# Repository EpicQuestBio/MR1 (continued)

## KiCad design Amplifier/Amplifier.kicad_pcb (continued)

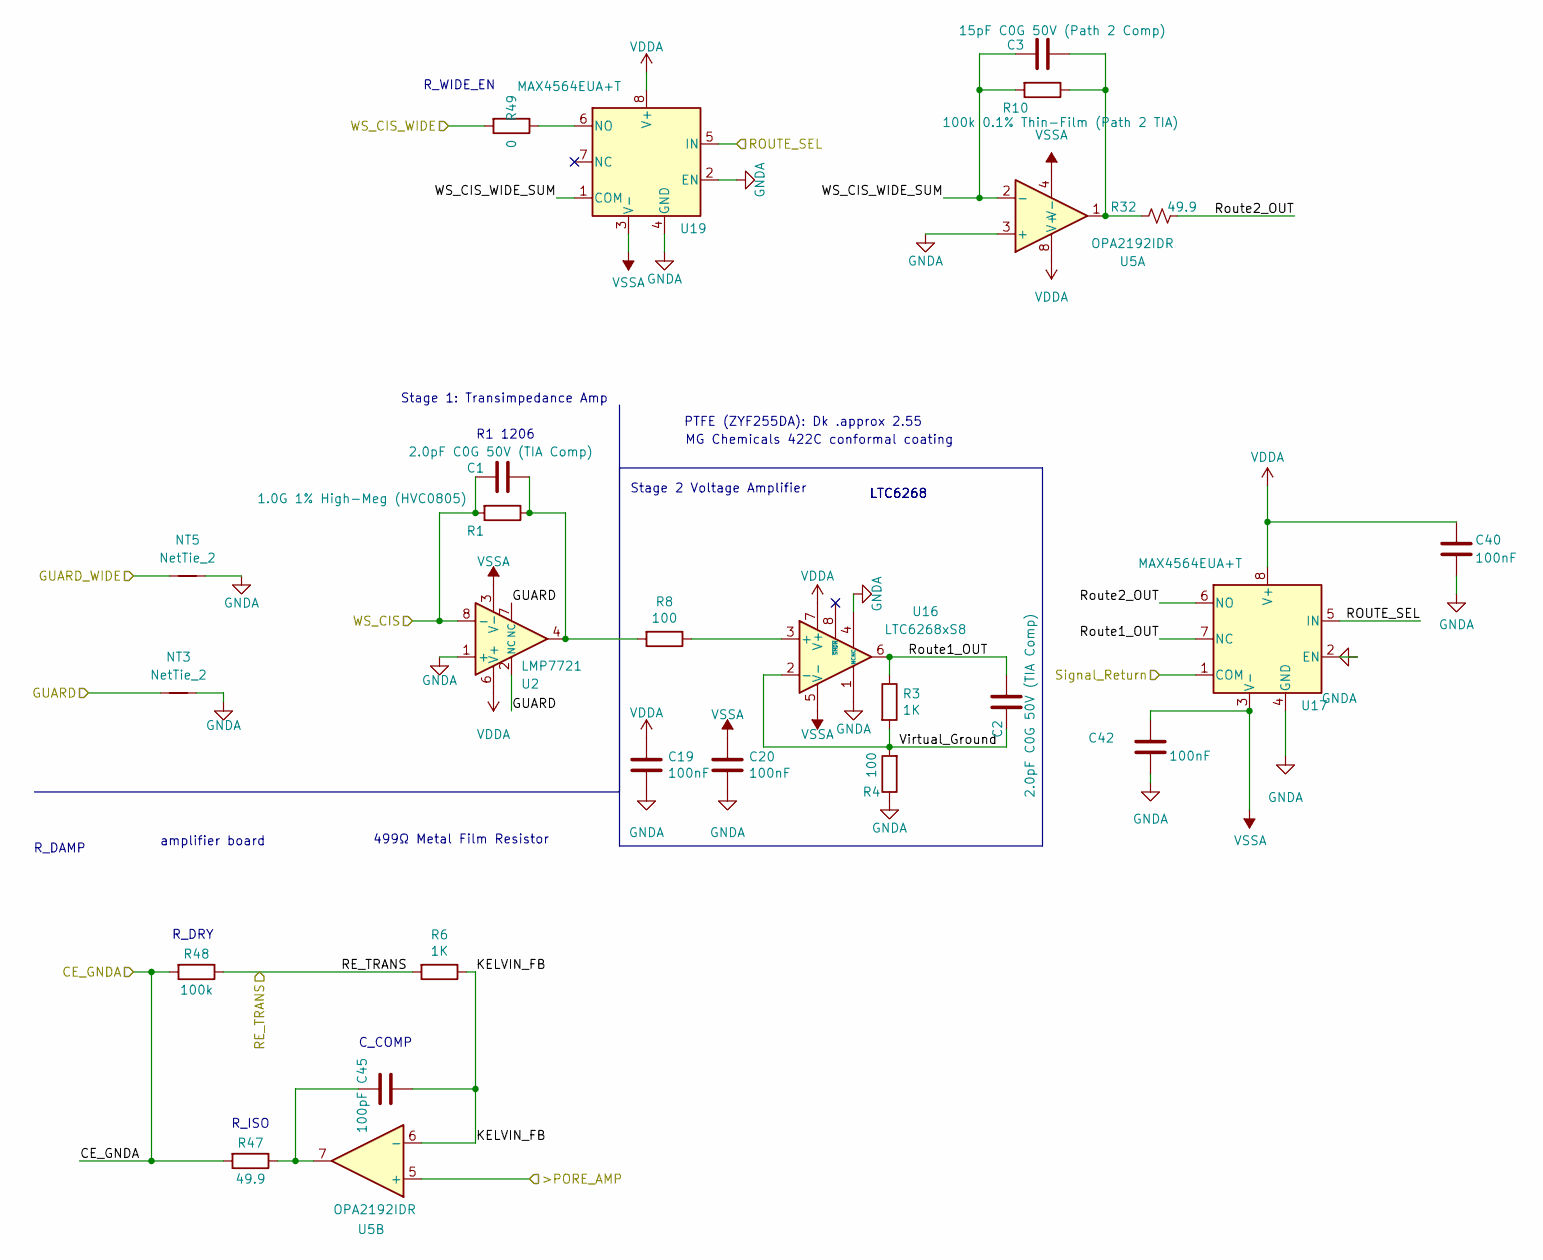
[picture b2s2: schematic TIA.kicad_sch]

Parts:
C1, C2: 2.0pF C0G 50V (TIA Comp); C_0402_1005Metric; LCSC C161316
C3: 15pF C0G 50V (Path 2 Comp); C_0402_1005Metric; LCSC C1548
C19, C20: 100nF; C_0402_1005Metric; LCSC C1525
C40, C42: 100nF; C_0402_1005Metric; Mouser PN 710-885012205037; LCSC C1525
C45: 100pF; C_0402_1005Metric; MPN GRM1555C1H101JA01D; LCSC C1546
NT3, NT5: NetTie_2; NetTie-2_SMD_Pad0.5mm
R1: 1.0G 1% High-Meg (HVC0805); R_0805_2012Metric; LCSC HVC0805T1007JET
R3, R6: 1K; R_0402_1005Metric; LCSC C11702
R4, R8: 100; R_0402_1005Metric; LCSC C25076
R10: 100k 0.1% Thin-Film (Path 2 TIA); R_0402_1005Metric; LCSC C60491
R32: 49.9; R_0402_1005Metric; MPN RC0402JR-0727RL; LCSC C87044
R47: 49.9; R_0402_1005Metric; MPN RC0402FR-0749R9L; LCSC C87044
R48: 100k; R_0402_1005Metric; MPN RC0402FR-07100KL; LCSC C60491
R49: 0; R_0402_1005Metric; MPN RC0402JR-070RL; LCSC C17168
U2: LMP7721; SOIC-8_3.9x4.9mm_P1.27mm; Mouser PN 926-LMP7721MA/NOPB
U5: OPA2192IDR; SOIC-8_3.9x4.9mm_P1.27mm; MPN OPA2192IDR; LCSC C110074
U16: LTC6268xS8; SO-8_3.9x4.9mm_P1.27mm; MPN LTC6268IS8#TRPBF; LCSC C689169
U17, U19: MAX4564EUA+T; MSOP-8_3x3mm_P0.65mm; MPN MAX4564EUA+T; Mouser PN 700-MAX4564EUA+

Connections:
/>PORE_AMP: U5.5 (+); also elsewhere on the board
/CE_GNDA: R47.2, R48.2; also elsewhere on the board
/GUARD: NT3.1, U2.2 (NC), U2.7 (NC); also elsewhere on the board
/GUARD_WIDE: NT5.1; also elsewhere on the board
/RE_TRANS: R6.2, R48.1; also elsewhere on the board
/ROUTE_SEL: U17.5 (IN), U19.5 (IN); also elsewhere on the board
/Signal_Return: U17.1 (COM); also elsewhere on the board
/TIA/KELVIN_FB: C45.2, R6.1, U5.6 (-)
/TIA/Route1_OUT: C2.1, R3.1, U16.6, U17.7 (NC)
/TIA/Route2_OUT: R32.2, U17.6 (NO)
/TIA/Virtual_Ground: C2.2, R3.2, R4.2, U16.2 (-)
/TIA/WS_CIS_WIDE_SUM: C3.2, R10.2, U5.2 (-), U19.1 (COM)
/WS_CIS: C1.2, R1.2, U2.8 (-); also elsewhere on the board
/WS_CIS_WIDE: R49.2; also elsewhere on the board
GNDA: C19.2, C20.2, C40.2, C42.2, NT3.2, NT5.2, R4.1, U2.1 (+), U5.3 (+), U16.1 (NC), U16.4 (NC), U17.2 (EN), U17.4 (GND), U19.2 (EN), U19.4 (GND); also elsewhere on the board
unnamed: C1.1, R1.1, R8.2, U2.4
unnamed: C3.1, R10.1, R32.1, U5.1
unnamed: C45.1, R47.1, U5.7
unnamed: R8.1, U16.3 (+)
unnamed: R49.1, U19.6 (NO)
VDDA: C19.1, C40.1, U2.6 (V+), U5.8 (V+), U16.7 (V+), U17.8 (V+), U19.8 (V+); also elsewhere on the board
VSSA: C20.1, C42.1, U2.3 (V-), U5.4 (V-), U16.5 (V-), U17.3 (V-), U19.3 (V-); also elsewhere on the board

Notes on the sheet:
amplifier board
R_DAMP
LTC6268
499Ω Metal Film Resistor
C_COMP
R1 1206
PTFE (ZYF255DA): Dk .approx 2.55
R_WIDE_EN
Stage 1: Transimpedance Amp
R_DRY
MG Chemicals 422C conformal coating
R_ISO
Stage 2 Voltage Amplifier

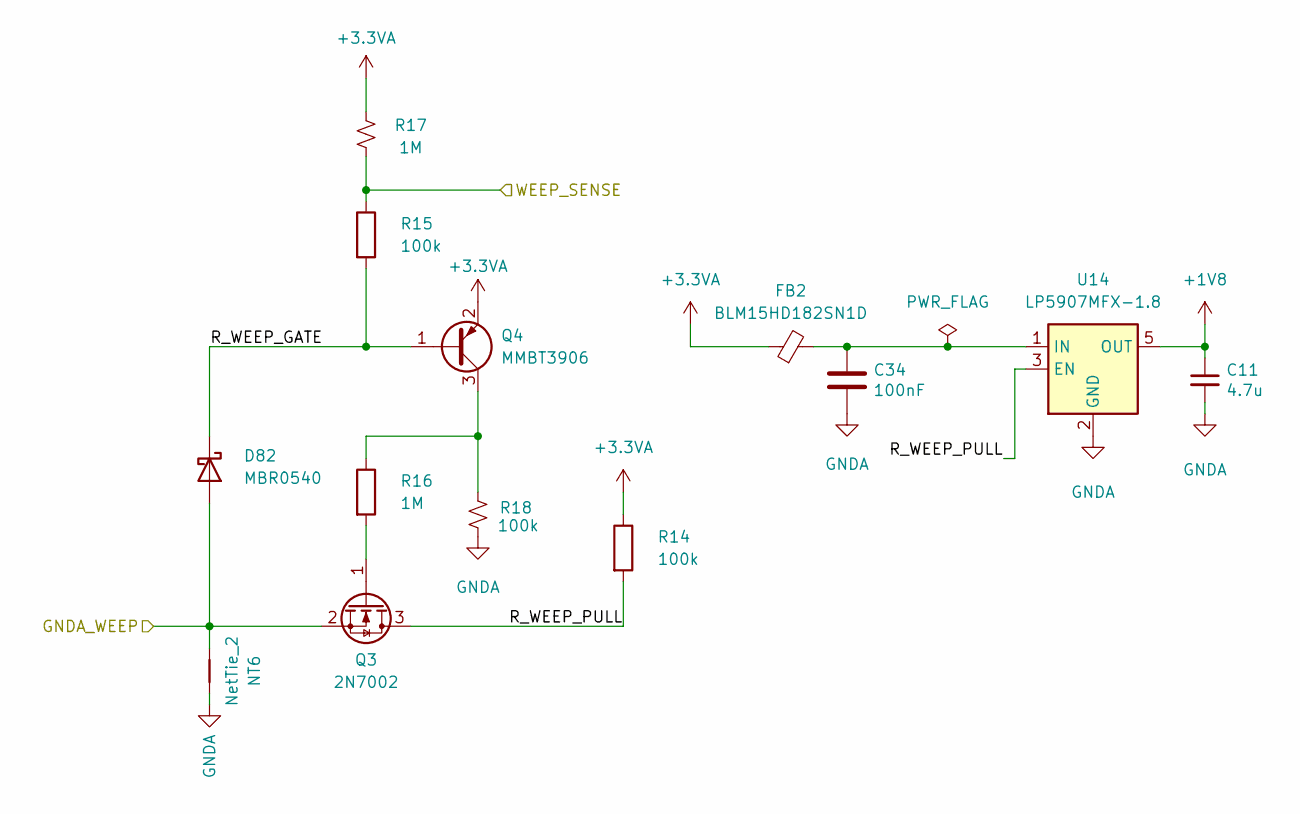
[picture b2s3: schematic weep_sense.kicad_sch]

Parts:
C11: 4.7u; C_0402_1005Metric; Manufacturer_Part_Number JMK107C6475KA-T; LCSC C23733
C34: 100nF; C_0402_1005Metric; LCSC C1525
D82: MBR0540; D_SOD-123; MPN 0402B473K500NT; LCSC C5204747
FB2: BLM15HD182SN1D; L_0402_1005Metric; LCSC C76888
NT6: NetTie_2; NetTie-2_SMD_Pad0.5mm
Q3: 2N7002; SOT-23; LCSC C8545
Q4: MMBT3906; SOT-23; MPN MMBT3906; LCSC C2143
R14, R15: 100k; R_0402_1005Metric; LCSC C60491
R16: 1M; R_0402_1005Metric; LCSC C26083
R17: 1M; R_0402_1005Metric; MPN 0402WGF1004TCE; LCSC C26083
R18: 100k; R_0402_1005Metric; MPN 0402WGF1003TCE; LCSC C60491
U14: LP5907MFX-1.8; SOT-23-5; MPN LP5907MFX-1.8/NOPB; LCSC C92498

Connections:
+1V8: C11.1, U14.5 (OUT); also elsewhere on the board
+3.3VA: FB2.1, Q4.2 (E), R14.1, R17.1; also elsewhere on the board
/GNDA_WEEP: D82.2 (A), NT6.1, Q3.2 (S); also elsewhere on the board
/WEEP_SENSE: R15.1, R17.2; also elsewhere on the board
/weep_sense/R_WEEP_GATE: D82.1 (K), Q4.1 (B), R15.2
/weep_sense/R_WEEP_PULL: Q3.3 (D), R14.2, U14.3 (EN)
GNDA: C11.2, C34.2, NT6.2, R18.2, U14.2 (GND); also elsewhere on the board
unnamed: Q3.1 (G), R16.2
unnamed: Q4.3 (C), R16.1, R18.1
unnamed: C34.1, FB2.2, U14.1 (IN)

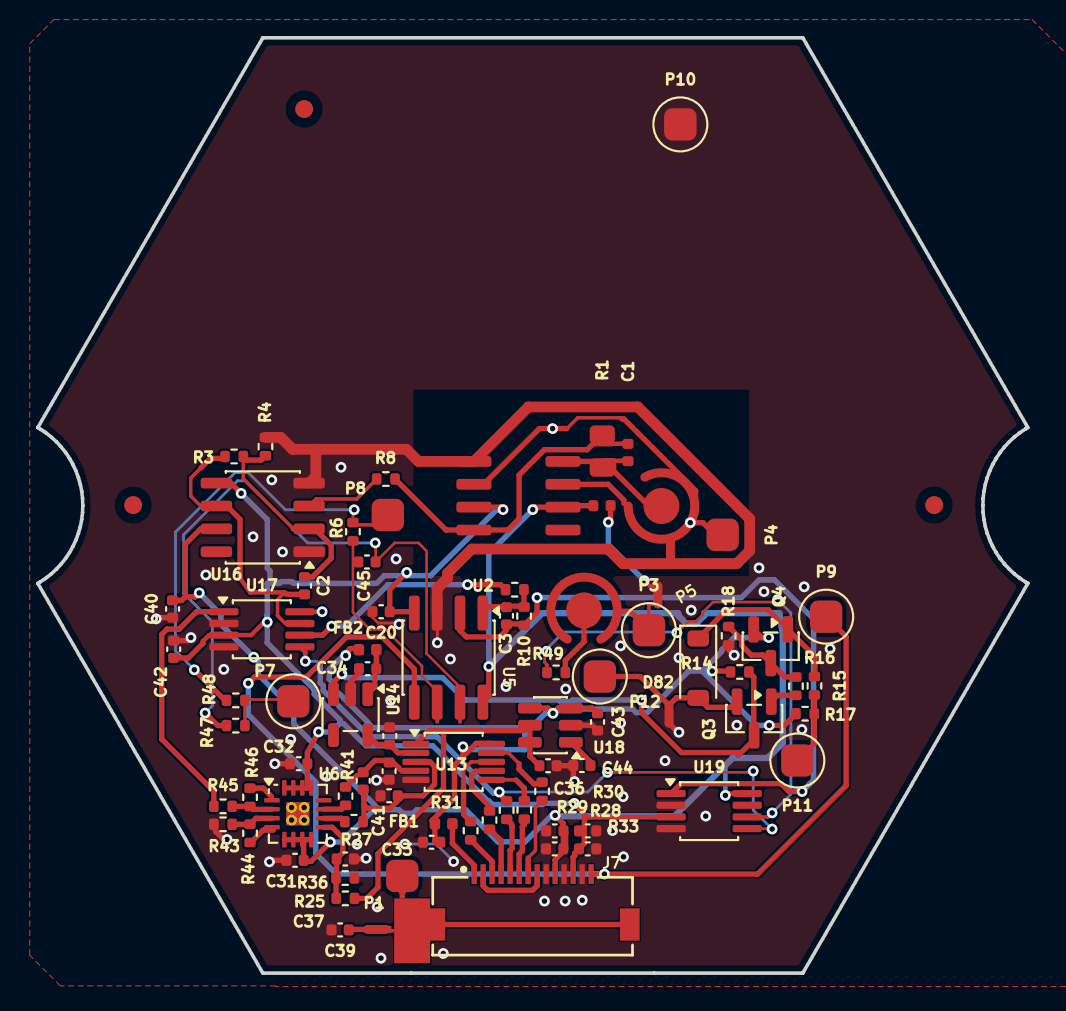
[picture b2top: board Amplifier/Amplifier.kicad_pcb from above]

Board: 4 copper layers, 55.0 x 52.0 mm, 88 parts (1 on the bottom side), 57 nets.

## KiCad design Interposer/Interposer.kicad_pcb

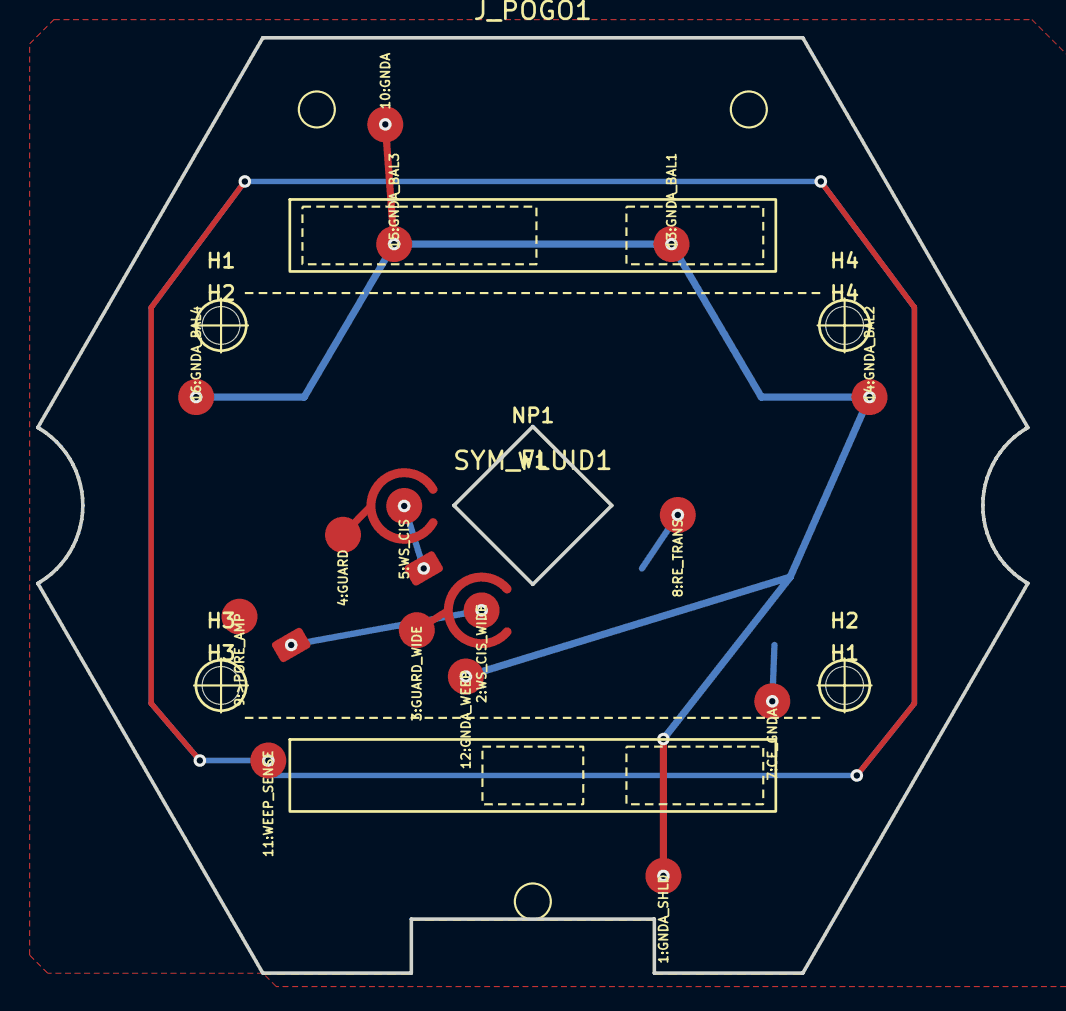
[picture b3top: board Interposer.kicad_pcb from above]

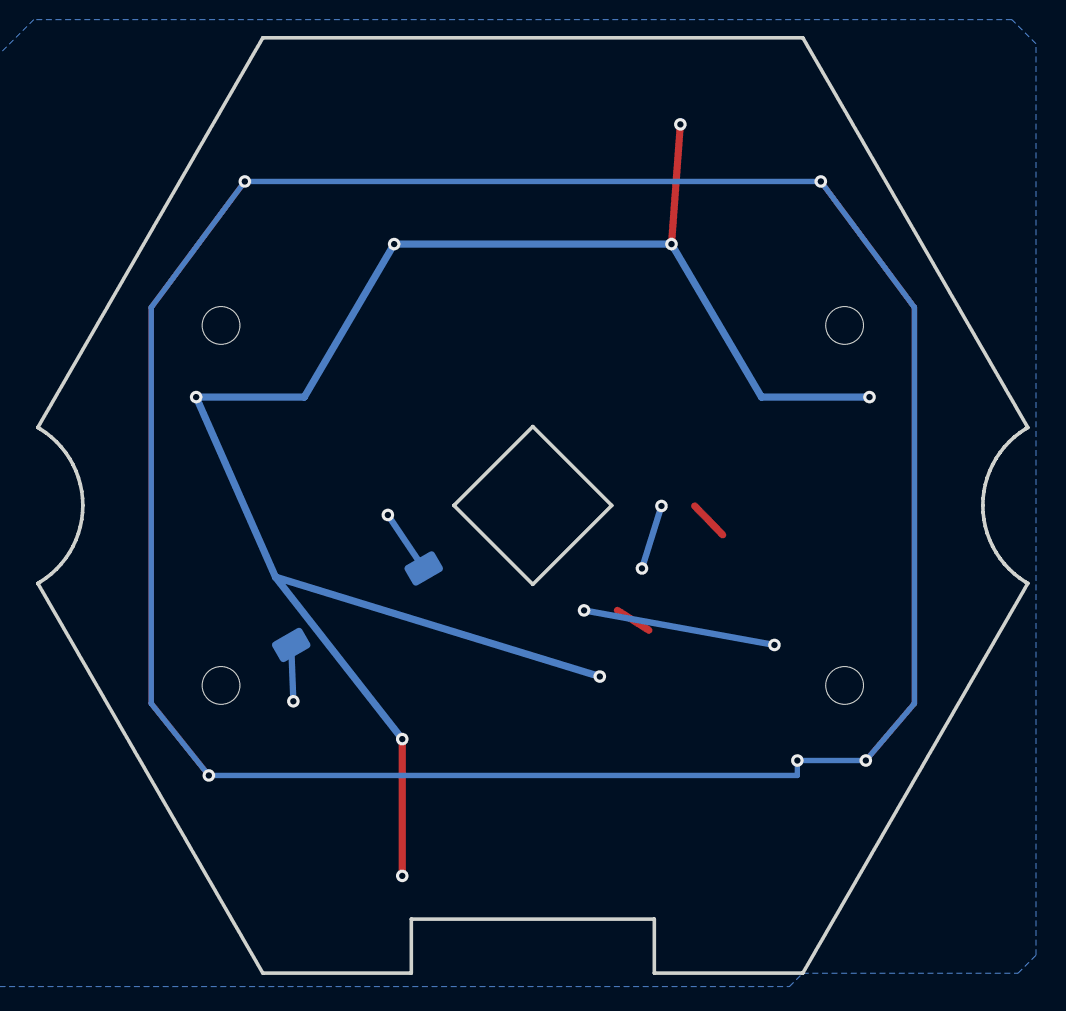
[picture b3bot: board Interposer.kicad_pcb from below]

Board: 2 copper layers, 55.0 x 52.0 mm, 12 parts (2 on the bottom side), 5 nets.

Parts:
H1: Port_Trans_In_H1; Fluidic_Port_PassThrough_5mm
H2: Port_Trans_Out_H2; Fluidic_Port_PassThrough_5mm
H3: Port_Cis_In_H3; Fluidic_Port_PassThrough_5mm
H4: Port_Cis_Out_H4; Fluidic_Port_PassThrough_5mm
J1: Cis_Sense_AgAgCl; Electrode_Guard_Shield
J2: Cis_Drive_AgAgCl; Electrode_Guard_Shield
J10: Trans_Drive_AgAgCl; Electrode_Guard_Shield
J11: Trans_Sense_AgAgCl; Electrode_Guard_Shield
J_POGO1: PogoPin_Target_12Pin_Distributed
NP1: Nanopore_Wafer_Aperture; Nanopore holder_recessed
SYM_FLUID1: Fluid_Overlay_SILKSCREEN_ONLY
W1: Weep_Moat_Sensor

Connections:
CE_GNDA: J10.1, J_POGO1.7
GNDA: J_POGO1.1, J_POGO1.10, J_POGO1.12, J_POGO1.13, J_POGO1.14, J_POGO1.15, J_POGO1.16
RE_TRANS: J11.1, J_POGO1.8
WS_CIS: J1.1, J_POGO1.5
WS_CIS_WIDE: J2.1, J_POGO1.2

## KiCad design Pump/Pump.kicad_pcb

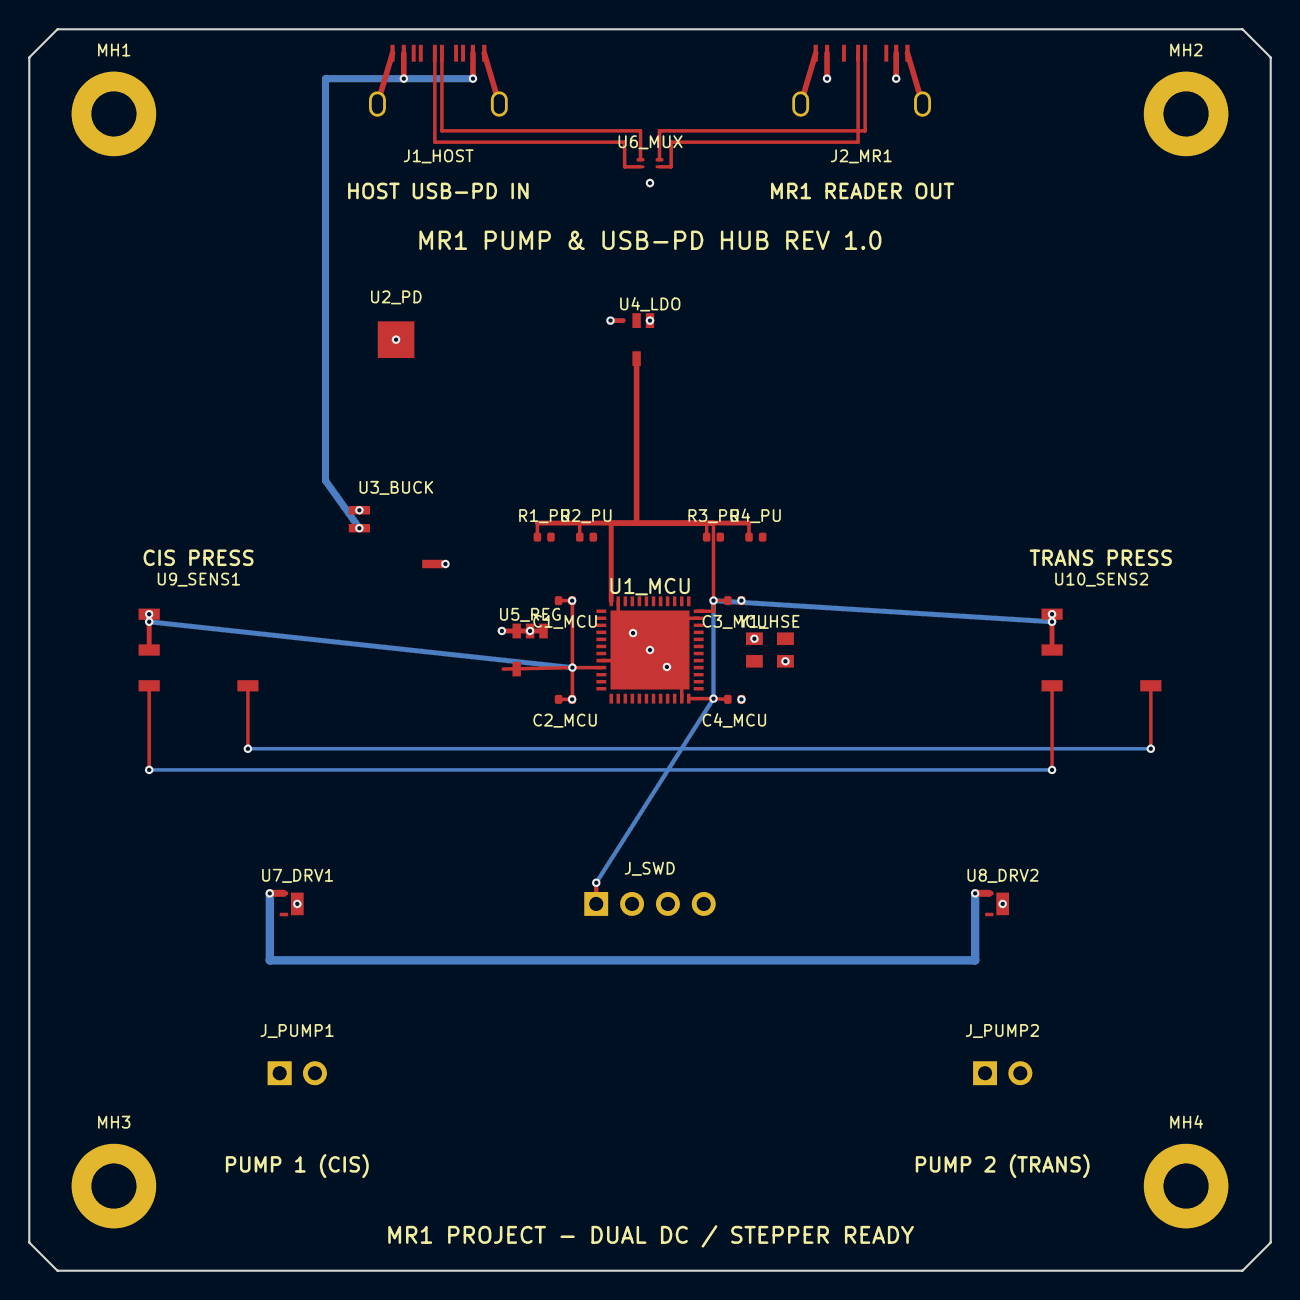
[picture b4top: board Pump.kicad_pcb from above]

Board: 4 copper layers, 88.0 x 88.0 mm, 28 parts (0 on the bottom side), 11 nets.

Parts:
C1_MCU, C2_MCU, C3_MCU, C4_MCU: 100nF; C_0402_1005Metric
J1_HOST: USB_C_HOST; USB_C_Receptacle_GCT_USB4085
J2_MR1: USB_C_MR1_OUT; USB_C_Receptacle_GCT_USB4085
J_PUMP1, J_PUMP2: PUMP_MOTOR; JST_XH_B2B-XH-A_1x02_P2.50mm_Vertical
J_SWD: PinHeader_1x04_P2.54mm_Vertical
MH1, MH2, MH3, MH4: MountingHole_3.2mm_M3_Pad
R1_PU, R2_PU, R3_PU, R4_PU: 4.7k; R_0402_1005Metric
U1_MCU: STM32G431CBU6; QFN-48-1EP_7x7mm_P0.5mm_EP5.6x5.6mm
U2_PD: STUSB4500; QFN-24-1EP_4x4mm_P0.5mm_EP2.6x2.6mm
U3_BUCK: TPS54302; SOIC-8_3.9x4.9mm_P1.27mm
U4_LDO: LD39050_3V3; SOT-23-5
U5_REG: TLV70233_3V3_ANA; SOT-23-5
U6_MUX: TS3USB221; Texas_UQFN-10_1.5x2mm_P0.5mm
U7_DRV1, U8_DRV2: DRV8837C; Texas_DSG0008A_WSON-8-1EP_2x2mm_P0.5mm_EP0.9x1.6mm
U9_SENS1: ABP2_015PG_CIS; Honeywell_ABP_SMD
U10_SENS2: ABP2_005PG_TRANS; Honeywell_ABP_SMD
Y1_HSE: 8.000MHz; Crystal_SMD_3225-4Pin_3.2x2.5mm

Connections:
+3V3: C1_MCU.1, C2_MCU.1, C3_MCU.1, C4_MCU.1, J_SWD.1, R1_PU.1, R2_PU.1, R3_PU.1, R4_PU.1, U1_MCU.9, U1_MCU.24, U1_MCU.36, U1_MCU.48, U4_LDO.5, U5_REG.5, U9_SENS1.2, U10_SENS2.2
+5V_MR1_CLEAN: J2_MR1.A4, J2_MR1.A9, U3_BUCK.5, U4_LDO.1, U5_REG.1, U5_REG.3
+VBUS_PD: J1_HOST.A4, J1_HOST.A9, U3_BUCK.2
GND: C1_MCU.2, C2_MCU.2, C3_MCU.2, C4_MCU.2, J1_HOST.A1, J1_HOST.A12, J1_HOST.SH1, J1_HOST.SH2, J2_MR1.A1, J2_MR1.A12, J2_MR1.SH1, J2_MR1.SH2, J_SWD.4, MH1.1, MH2.1, MH3.1, MH4.1, U1_MCU.8, U1_MCU.23, U1_MCU.35, U1_MCU.47, U1_MCU.49, U2_PD.25, U3_BUCK.1, U4_LDO.2, U5_REG.2, U6_MUX.5, U7_DRV1.4, U7_DRV1.9, U8_DRV2.4, U8_DRV2.9, U9_SENS1.1, U10_SENS2.1, Y1_HSE.2, Y1_HSE.4
HOST_D+: J1_HOST.A6, U6_MUX.1
HOST_D-: J1_HOST.A7, U6_MUX.2
MR1_D+: J2_MR1.A6, U6_MUX.10
MR1_D-: J2_MR1.A7, U6_MUX.9
PRESS_I2C_SCL: U9_SENS1.4, U10_SENS2.4
PRESS_I2C_SDA: U9_SENS1.3, U10_SENS2.3
VMOTOR: U7_DRV1.1, U8_DRV2.1

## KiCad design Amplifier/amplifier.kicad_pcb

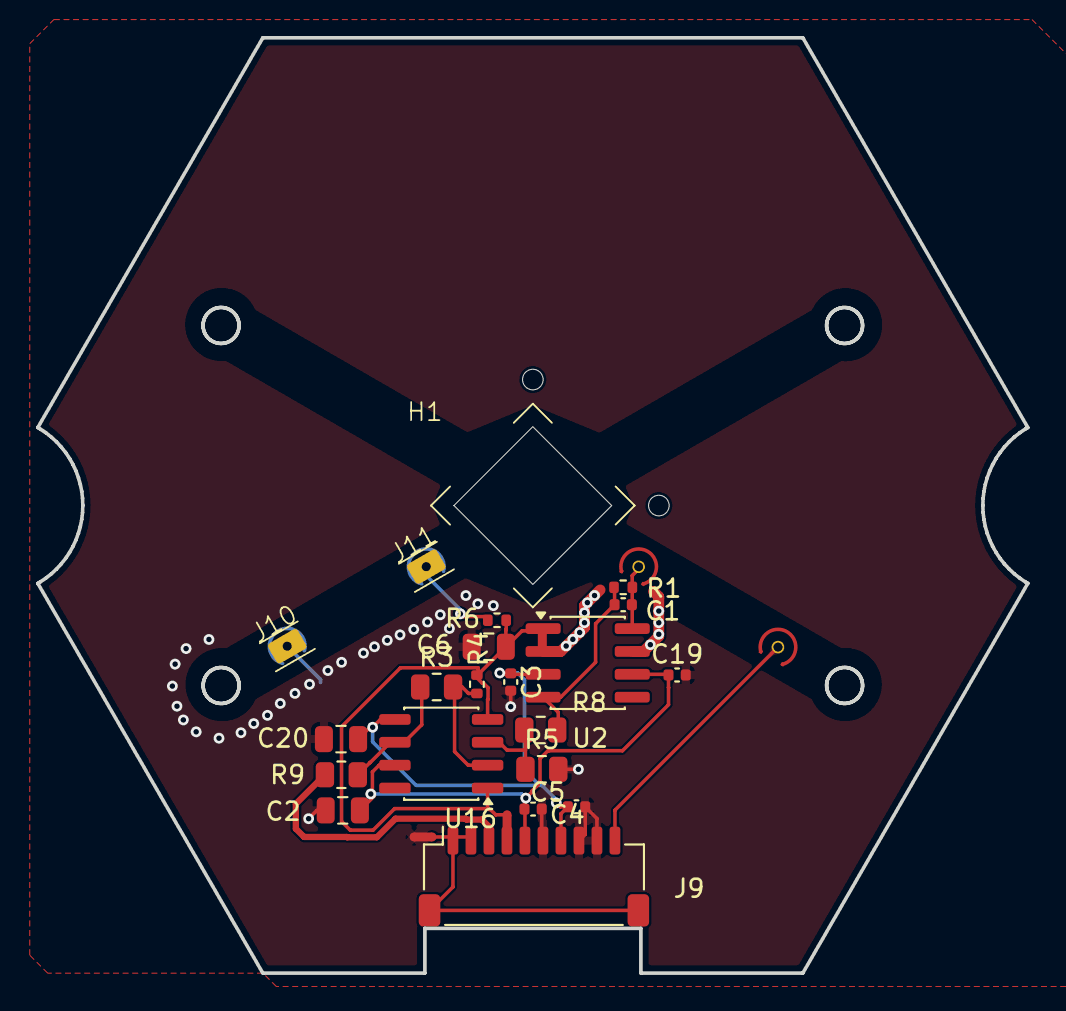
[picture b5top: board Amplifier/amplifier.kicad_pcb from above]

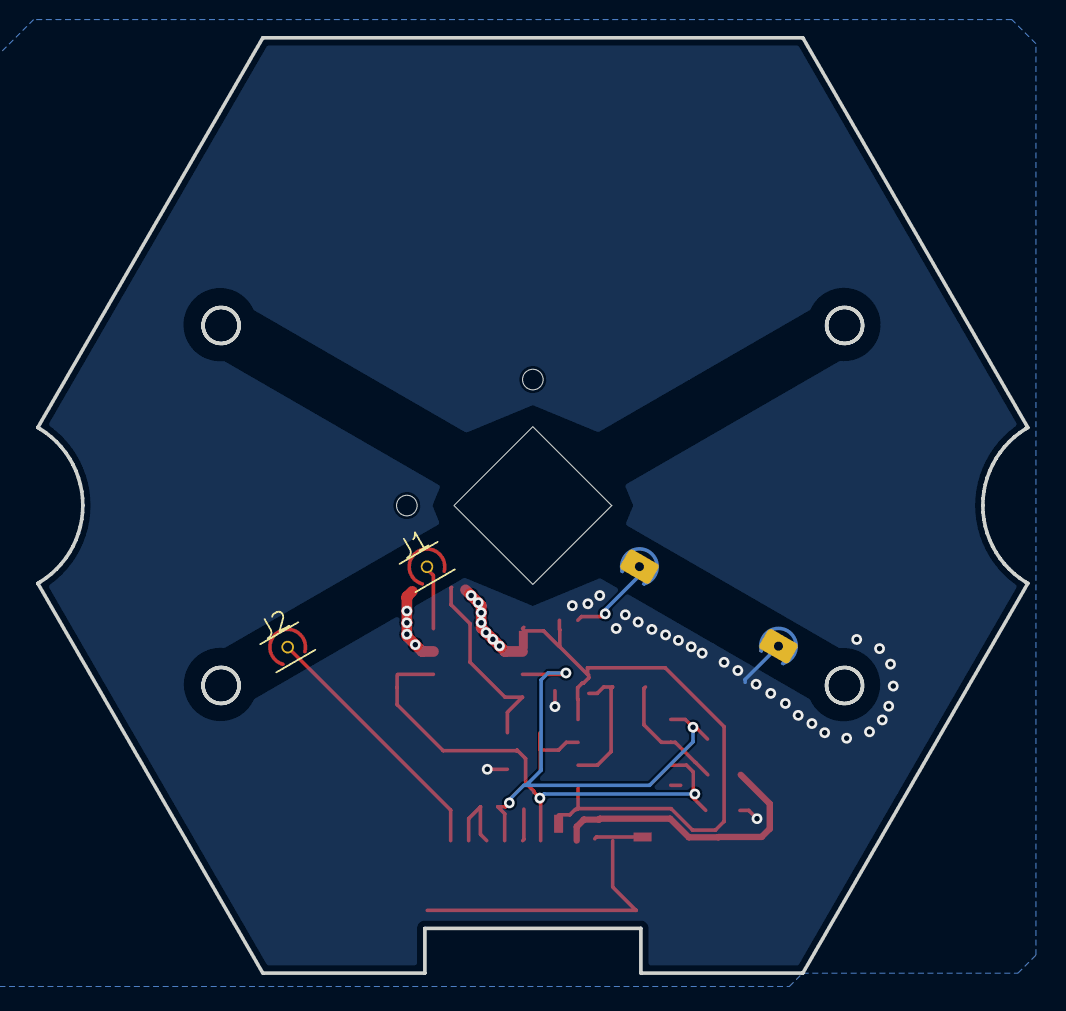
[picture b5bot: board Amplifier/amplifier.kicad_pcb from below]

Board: 2 copper layers, 55.0 x 52.0 mm, 26 parts (2 on the bottom side), 15 nets.

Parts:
C1: 2pF; C_0402_1005Metric
C2, C6, C20: 100nF; C_0805_2012Metric
C3, C19: 100nF; C_0402_1005Metric
C4, C5: 10nF; C_0402_1005Metric
H1: Nanopore; Nanopore holder_recessed
J1, J2, J10, J11: Conn_01x01_Pin; Electrode_Guard_Shield
J9: Conn_01x10; JST_SH_SM10B-SRSS-TB_1x10-1MP_P1.00mm_Horizontal
NT3, NT4, NT5: NetTie_2; NetTie-2_SMD_Pad0.5mm
R1: 1M; R_0402_1005Metric
R3, R5: 1K; R_0805_2012Metric
R4: 100; R_0402_1005Metric
R6: 1K; R_0402_1005Metric
R8, R9: 100; R_0805_2012Metric
U2: LMP7721; SOIC-8_3.9x4.9mm_P1.27mm
U16: LTC6268xS8; SO-8_3.9x4.9mm_P1.27mm

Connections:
/>PORE_AMP: J2.1 (In), J9.10
/GUARD: J1.2 (Ext), NT3.1, U2.2 (NC), U2.7 (NC)
/SHIELD_AMP: J9.1, J9.2, J9.MP (Pin_11), NT4.2
/Signal_AMP: J9.3, R9.1
/Vbias: C6.1, NT3.2, NT5.1, R4.1, R6.1, U2.1 (+), U16.1 (NC), U16.4 (NC)
/Vbias_AMP: J9.4, NT5.2
GNDA: C2.2, C3.2, C4.2, C5.2, C6.2, C19.2, C20.2, J2.2 (Ext), J9.6, J9.8, J9.9, J10.1 (In), J10.2 (Ext), J11.2 (Ext), NT4.1, R5.2
unnamed: C1.1, R1.1, R8.2, U2.4
unnamed: C1.2, J1.1 (In), R1.2, U2.8 (-)
unnamed: J11.1 (In), R6.2
unnamed: R3.1, R9.2, U16.6
unnamed: R5.1, R8.1, U16.3 (+)
unnamed: R3.2, R4.2, U16.2 (-)
VDDA: C2.1, C4.1, C19.1, J9.5, U2.6 (V+), U16.7 (V+)
VSSA: C3.1, C5.1, C20.1, J9.7, U2.3 (V-), U16.5 (V-)

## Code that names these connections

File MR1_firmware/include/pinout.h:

/*
 * Created by Lawrence R. Kincheloe III / Molecular Reality Corp (2026).
 * Dedicated to the public domain under CC0 1.0 Universal (CC0-1.0).
 * SPDX-License-Identifier: CC0-1.0
 */

/**
 * @file pinout.h
 * @brief Canonical Hardware Pin Mapping for MR1 Nanopore Reader (MR1 Board)
 * 
 * Target MCU: ESP32-S3-MINI-1U
 * Schematics: MR1 (Microcontroller, Ignition, Insturmentation, Power)
 */

#pragma once

#include <stdint.h>

// =============================================================================
// Analog-to-Digital Converter & Readout Route Selection
// =============================================================================
#define PIN_ADC_CNV          5  // Conversion Start / Chip Select (Net: /Insturmentation/ADC_EN via R36)
#define PIN_ADC_SCK          8  // Serial Clock up to 40MHz (Net: /Insturmentation/ADC_CLK via R37)
#define PIN_ADC_SDO          6  // Serial Data Out / MISO (Net: /Insturmentation/ADC_SDO via R10)
#define PIN_ADC_SDI          4  // Serial Data In / MOSI (Net: /Insturmentation/ADC_SDI via R33)
#define PIN_ROUTE_SEL        7  // Readout Route Multiplexer Select (Net: /Insturmentation/ROUTE_SEL via R27)

// =============================================================================
// Digital-to-Analog Converter (MCP4822 - U9 on Ignition)
// =============================================================================
#define PIN_DAC_CS          12  // Chip Select (Active Low) (Net: /Ignition/CS_ via R41)
#define PIN_DAC_SCK         11  // Serial Clock (Net: /Ignition/SCK via R28)
#define PIN_DAC_SDI         10  // Serial Data In / MOSI (Net: /Ignition/SDI via R40)
#define PIN_DAC_LDAC         9  // Latch Update (Active Low) (Net: /Ignition/LDAC_ via R39)

// =============================================================================
// Native USB Interface (J3 Receptacle)
// =============================================================================
#define PIN_USB_DM          19  // USB D- (Net: /Power/D- via R16)
#define PIN_USB_DP          20  // USB D+ (Net: /Power/D+ via R15)

// =============================================================================
// USB-C Sideband Use (SBU) & I2C Auto-Polarity Interface
// =============================================================================
#define PIN_USB_SBU1        21  // USB-C SBU1 (Pin A8 via R53)
#define PIN_USB_SBU2        26  // USB-C SBU2 (Pin B8 via R54)
#define PIN_SBU_MUX_SEL     14  // Hardware cross-multiplexer select (optional)

// =============================================================================
// External Peristaltic Pump Port (J22 - B4B-PH Connector)
// =============================================================================
#define PIN_PUMP_TX         33  // UART TX to Pump Module (J22 Pin 2 via GPIO33)
#define PIN_PUMP_RX         47  // UART RX from Pump Module (J22 Pin 3 via GPIO47)
#define PUMP_UART_NUM        1  // Hardware UART Port 1

// =============================================================================
// Safety & Power Supervision (Power Good Monitors & Fault Interlocks)
// =============================================================================
#define PIN_PG_VSSA          1  // Power Good negative supply (Net: /Power/PG_VSSA via R57)
#define PIN_PG_VDDA          2  // Power Good positive supply (Net: /Power/PG_VDDA via R58)
#define PIN_PG_CP            3  // Power Good charge pump LM27762 (Net: /Power/PG_CP via R59)
#define PIN_LEAK_SENSE       PIN_PG_VSSA  // VSSA power rail fault trips emergency shutoff

// =============================================================================
// Host / Debug UART (Optional Header / Programming Console)
// =============================================================================
#define PIN_DEBUG_TX        43  // TXD0
#define PIN_DEBUG_RX        44  // RXD0

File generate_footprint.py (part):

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generate_footprint.py
=====================
Extracts mechanical geometry, fluidic manifold coordinates, concentric
compression electrode guard rings, and 12-pin distributed pogo-pin target
locations directly from the `build123d` CAD models (`src.cartridge`,
`src.common`, `src.constants`, `src.nanopore_wafer_mold`) and generates the
production-ready KiCad 8/9 footprint:
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# P1: GNDA_SHLD (-18, +16 CAD), P2: WS_CIS_WIDE (-10, +15 CAD), P3: GUARD_WIDE (-6, +15 CAD),
# P4: GUARD_CIS_A (+4, +15 CAD), P5: WS_CIS (+8, +15 CAD), P6: GUARD_CIS_B (+12, +15 CAD)
PIN_NET_SEQUENCE_6PIN_CIS: List[Tuple[int, str, float, float, str]] = [
    (1, "GNDA_SHLD", -18.0, 16.0, "Shield anchor pinning inlet/outlet fluid manifold ground boundary"),
    (2, "WS_CIS_WIDE", -10.0, 15.0, "Path 2 (200 nm Pore) working electrode contact; short straight escape"),
    (3, "GUARD_WIDE", -6.0, 15.0, "Active driven guard for Path 2; isolates Path 2 from Path 1 sensing"),
    (4, "GUARD_CIS_A", 4.0, 15.0, "Driven Guard (Left wing of triaxial Faraday cocoon around P5)"),
    (5, "WS_CIS", 8.0, 15.0, "Path 1 (Sub-5 nm Pore) high-Z electrometer node (LMP7721 Pin 8)"),
    (6, "GUARD_CIS_B", 12.0, 15.0, "Driven Guard (Right wing of triaxial Faraday cocoon around P5)"),
]

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# Exact 12-connection Distributed 2 x 6 Pogo Pin Map (6 Bank B Cis at CAD Y > 0 + 6 Bank A Trans at CAD Y < 0)
PIN_NET_SEQUENCE: List[Tuple[int, str, float, float, str]] = [
    # Bank B (Cis / Sensing - Pins 1..6)
    (1, "GNDA_SHLD", -18.0, 16.0, "Pin 1: Shield anchor pinning inlet/outlet fluid manifold ground boundary"),
    (2, "WS_CIS_WIDE", -10.0, 15.0, "Pin 2: Path 2 (200 nm Pore) working electrode contact"),
    (3, "GUARD_WIDE", -6.0, 15.0, "Pin 3: Active driven guard for Path 2"),
    (4, "GUARD_CIS_A", 4.0, 15.0, "Pin 4: Driven Guard (Left wing of triaxial Faraday cocoon around P5)"),
    (5, "WS_CIS", 8.0, 15.0, "Pin 5: Path 1 (Sub-5 nm Pore) high-Z electrometer node"),
    (6, "GUARD_CIS_B", 12.0, 15.0, "Pin 6: Driven Guard (Right wing of triaxial Faraday cocoon around P5)"),
    # Bank A (Trans / Excitation - Pins 7..12)
    (7, "CE_GNDA", -18.0, -16.0, "Pin 7: Trans Counter Electrode return path"),
    (8, "RE_TRANS", -10.0, -15.0, "Pin 8: Trans bulk reference sense node"),
    (9, ">PORE_AMP", -4.0, -15.0, "Pin 9: Active bias excitation drive"),
    (10, "GNDA", 3.0, -15.0, "Pin 10: Low-noise analog ground return fence"),
    (11, "WEEP_SENSE", 12.0, -15.0, "Pin 11: Moisture-sensing trace intercepting droplet breaches"),
    (12, "GNDA_WEEP", 18.0, -16.0, "Pin 12: Perimeter weep moat static drain & outer chassis tie"),
]

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    center: Tuple[float, float]
    signal_pin: str
    signal_net: str
    guard_pin: str
    guard_net: str
    gnd_pin: str
    gnd_net: str
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                center=(0.0, 0.0),
                signal_pin="2",
                signal_net=">PORE_AMP",
                guard_pin="4",
                guard_net="GUARD",
                gnd_pin="1",
                gnd_net="GNDA",
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                center=(0.0, 0.0),
                signal_pin="6",
                signal_net="WS_CIS",
                guard_pin="5",
                guard_net="GUARD",
                gnd_pin="1",
                gnd_net="CE_GNDA",
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                center=(10.0, 0.0),
                signal_pin="4",
                signal_net="WS_CIS_WIDE",
                guard_pin="3",
                guard_net="GUARD_WIDE",
                gnd_pin="1",
                gnd_net="CE_GNDA",
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                center=(0.0, 0.0),
                signal_pin="12",
                signal_net="WS_CIS",
                guard_pin="11",
                guard_net="GUARD",
                gnd_pin="1",
                gnd_net="GNDA",
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                center=(10.0, 0.0),
                signal_pin="10",
                signal_net="WS_CIS_WIDE",
                guard_pin="9",
                guard_net="GUARD_WIDE",
                gnd_pin="3",
                gnd_net="GNDA",
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            '  (descr "6-Pin Mill-Max 09xx Bias-Tail/Ball-Contact Bare ENIG/Hard Gold Pogo Target + Dual-Seal PDMS Weep Moat + Rigid Anvil Clamp (50-100kHz Sub-pA Nanopore)")'
        )
        lines.append(
            '  (tags "pogo target 6-pin mill-max 09xx bias-tail ball-contact enig guard weep-moat anvil build123d")'
        )
    else:
        lines.append(
            '  (descr "Dual 6-Pin (6 Cis + 6 Trans) Mill-Max 09xx Bias-Tail/Ball-Contact Bare ENIG/Hard Gold Pogo Target + 4x 2.1mm Fluid Pass-Throughs + Dual-Seal PDMS Weep Moats + Rigid Anvil Clamps")'
        )
        lines.append(
            '  (tags "pogo target 6-pin cis trans mill-max 09xx bias-tail ball-contact interposer nanopore guard concentric fluidic build123d")'
        )

    # Required KiCad 8/9 Library Properties
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        )

        if y_bank < 0:
            # Cis 6-pin guard envelopes around >PORE_AMP (-6.5, -15.0) and WEEP_SENSE (11.5, -15.0)
            lines.append(
                f'  (fp_rect (start -12.8 -16.6) (end 0.2 -13.4) (stroke (width 0.12) (type dash)) (fill none) (layer "F.SilkS") (uuid "{deterministic_uuid(f"{fp_name}_cis_pore_guard_env")}"))'
            )
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                f'  (fp_rect (start 5.2 -16.6) (end 12.8 -13.4) (stroke (width 0.12) (type dash)) (fill none) (layer "F.SilkS") (uuid "{deterministic_uuid(f"{fp_name}_cis_weep_guard_env")}"))'
            )
        else:
            # Trans 6-pin guard envelopes around GUARD_WIDE/WS_CIS_WIDE (-1.5..+1.5) and GUARD/WS_CIS (+6.5..+11.5)
            lines.append(
                f'  (fp_rect (start -2.8 13.4) (end 2.8 16.6) (stroke (width 0.12) (type dash)) (fill none) (layer "F.SilkS") (uuid "{deterministic_uuid(f"{fp_name}_trans_wide_guard_env")}"))'
            )
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
        # Concentric Active Driven Guard Ring (Unbroken custom ring pad)
        lines.append(
            f'  (pad "{ce.guard_pin}" smd custom '
            f"(at {fmt4(cx + guard_r)} {fmt4(cy)}) "
            f"(size 0.4 0.4) "
            f'(layers "F.Cu" "F.Mask") '
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    is_cis = bank_norm == "cis"
    seq = PIN_NET_SEQUENCE_6PIN_CIS if is_cis else PIN_NET_SEQUENCE_6PIN_TRANS
    ref_des = "J_POGO_CIS" if is_cis else "J_POGO_TRANS"
    bank_title = "CIS 6-Pin Bank (GNDA, >PORE_AMP, GNDA, GUARD, GNDA, WEEP_SENSE)" if is_cis else "TRANS 6-Pin Bank (CE_GNDA, RE_TRANS, GUARD_WIDE, WS_CIS_WIDE, GUARD, WS_CIS)"

    lines: List[str] = [
        f'(footprint "{footprint_name}" (version 20241229) (generator "generate_footprint.py")',
        '  (layer "F.Cu")',
        f'  (descr "6-Pin Bare Unmasked ENIG/Hard Gold Pogo Target Array [{bank_title}] for Mill-Max 09xx Bias-Tail/Ball-Contact Pins (Sub-pA 50-100kHz Nanopore, Dual-Seal PDMS Weep Moat, Rigid Anvil Support)")',
        f'  (tags "pogo landing array target 6-pin {bank_norm} mill-max 09xx bias-tail ball-contact enig hard-gold ptfe guard weep-moat anvil")',
        f'  (property "Reference" "{ref_des}"',
        "    (at 0.0 -3.2 0)",
        "    (unlocked yes)",
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    is_cis = bank_norm == "cis"
    seq = PIN_NET_SEQUENCE_6PIN_CIS if is_cis else PIN_NET_SEQUENCE_6PIN_TRANS
    ref_des = "J_POGO_CIS" if is_cis else "J_POGO_TRANS"
    bank_title = "CIS 6-Pin Bank (GNDA, >PORE_AMP, GNDA, GUARD, GNDA, WEEP_SENSE)" if is_cis else "TRANS 6-Pin Bank (CE_GNDA, RE_TRANS, GUARD_WIDE, WS_CIS_WIDE, GUARD, WS_CIS)"

    lines: List[str] = [
        f'(footprint "{footprint_name}" (version 20241229) (generator "generate_footprint.py")',
        '  (layer "F.Cu")',
        f'  (descr "Mill-Max 09xx Series (0906/0985) Gold-Plated Bias-Tail/Ball-Contact 6-Pin Spring Header [{bank_title}] Soldered to Bottom of Amplifier PCB (Sub-pA, 50-100kHz)")',
        f'  (tags "mill-max 09xx 0906 0985 bias-tail ball-contact spring pogo 6-pin {bank_norm} reader-lid guard low-leakage")',
        f'  (property "Reference" "{ref_des}"',
        "    (at 0.0 -3.2 0)",
        "    (unlocked yes)",
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        dot_str = f"Dot {ce.inner_dot_dia:.2f}mm"
        guard_str = f"ID {ce.guard_id:.1f}/OD {ce.guard_od:.1f}"
        out.append(
            f"{ce.signal_pin + '/' + ce.guard_pin:<6} | {ce.signal_net + '+' + ce.guard_net:<14} | "
            f"{'concentric ring':<18} | {coord_str:<22} | {dot_str:<18} | {guard_str:<18}"
        )

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
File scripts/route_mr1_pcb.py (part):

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    elements.append(build_segment(82.40, 84.95, 81.50, 86.51, "B.Cu", "/Power/PG_CP", get_id(), width=0.15))
    elements.append(build_via(81.50, 86.51, "/Power/PG_CP", get_id()))

    # 2. PG_VDDA: U4 pin 5 (71.1055, 83.0256) -> via (71.68, 83.0256) -> B.Cu (X=71.68 south to Y=84.40) -> east along Y=84.40 to (83.00, 84.40) -> (83.00, 86.51) into R45 Pad 2
    elements.append(build_segment(71.1055, 83.0256, 71.68, 83.0256, "F.Cu", "/Power/PG_VDDA", get_id(), width=0.15))
    elements.append(build_via(71.68, 83.0256, "/Power/PG_VDDA", get_id()))
    elements.append(build_segment(71.68, 83.0256, 71.68, 84.40, "B.Cu", "/Power/PG_VDDA", get_id(), width=0.15))
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    elements.append(build_segment(83.00, 84.40, 83.00, 86.51, "B.Cu", "/Power/PG_VDDA", get_id(), width=0.15))
    elements.append(build_via(83.00, 86.51, "/Power/PG_VDDA", get_id()))

    # 3. PG_VSSA: from U2 pin 4 (71.675, 78.585) -> via (73.00, 78.75) -> south along X=73.00 to Y=83.355 (clears shifted GNDA vias and -Vp track)
    elements.append(build_segment(71.675, 78.585, 72.50, 78.585, "F.Cu", "/Power/PG_VSSA", get_id(), width=0.15))
    elements.append(build_segment(72.50, 78.585, 72.665, 78.75, "F.Cu", "/Power/PG_VSSA", get_id(), width=0.15))
    elements.append(build_segment(72.665, 78.75, 73.00, 78.75, "F.Cu", "/Power/PG_VSSA", get_id(), width=0.15))
    elements.append(build_via(73.00, 78.75, "/Power/PG_VSSA", get_id()))
    elements.append(build_segment(73.00, 78.75, 73.00, 83.355026, "B.Cu", "/Power/PG_VSSA", get_id(), width=0.15))

    # O. Damping outputs to ESP32 (GPIO3, GPIO2, GPIO1) strictly planar
    # Column 1 (X=89.20): GPIO3 from R59 (X=81.5) -> via (81.5, 88.60) -> B.Cu (89.20, 88.60) -> peels off at Y=61.50 -> U8 pin 7 (88.969, 61.50)
    elements.append(build_segment(81.5, 88.71, 81.5, 88.60, "F.Cu", "/Microcontroller/GPIO3", get_id()))
    elements.append(build_via(81.5, 88.60, "/Microcontroller/GPIO3", get_id()))
    elements.append(build_segment(81.5, 88.60, 89.20, 88.60, "B.Cu", "/Microcontroller/GPIO3", get_id(), width=0.15))
    elements.append(build_segment(89.20, 88.60, 89.20, 61.50, "B.Cu", "/Microcontroller/GPIO3", get_id(), width=0.15))
    elements.append(build_via(89.20, 61.50, "/Microcontroller/GPIO3", get_id()))
    elements.append(build_segment(89.20, 61.50, 88.969, 61.50, "F.Cu", "/Microcontroller/GPIO3", get_id(), width=0.15))

    # Column 2 (X=89.55): GPIO2 from R58 (X=83.0) -> via (83.0, 89.15) -> B.Cu (89.55, 89.15) -> peels off at Y=60.65 -> U8 pin 6 (88.969, 60.65)
    elements.append(build_segment(83.0, 88.71, 83.0, 89.15, "F.Cu", "/Microcontroller/GPIO2", get_id()))
    elements.append(build_via(83.0, 89.15, "/Microcontroller/GPIO2", get_id()))
    elements.append(build_segment(83.0, 89.15, 89.55, 89.15, "B.Cu", "/Microcontroller/GPIO2", get_id(), width=0.15))
    elements.append(build_segment(89.55, 89.15, 89.55, 60.65, "B.Cu", "/Microcontroller/GPIO2", get_id(), width=0.15))
    elements.append(build_via(89.55, 60.65, "/Microcontroller/GPIO2", get_id()))
    elements.append(build_segment(89.55, 60.65, 88.969, 60.65, "F.Cu", "/Microcontroller/GPIO2", get_id(), width=0.15))

    # Column 3 (X=89.90): GPIO1 from R57 (X=84.5) -> via (84.5, 89.70) -> B.Cu (89.90, 89.70) -> peels off at Y=59.80 -> U8 pin 5 (88.969, 59.80)
    elements.append(build_segment(84.5, 88.71, 84.5, 89.70, "F.Cu", "/Microcontroller/GPIO1", get_id()))
    elements.append(build_via(84.5, 89.70, "/Microcontroller/GPIO1", get_id()))
    elements.append(build_segment(84.5, 89.70, 89.90, 89.70, "B.Cu", "/Microcontroller/GPIO1", get_id(), width=0.15))
    elements.append(build_segment(89.90, 89.70, 89.90, 59.80, "B.Cu", "/Microcontroller/GPIO1", get_id(), width=0.15))
    elements.append(build_via(89.90, 59.80, "/Microcontroller/GPIO1", get_id()))
    elements.append(build_segment(89.90, 59.80, 88.969, 59.80, "F.Cu", "/Microcontroller/GPIO1", get_id(), width=0.15))

    # P. +Vp_cm jumper on B.Cu replacing F.Cu track:
    elements.append(build_via(78.00, 82.15, "/Power/+Vp_cm", get_id()))
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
